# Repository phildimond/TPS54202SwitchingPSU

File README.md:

5V 2A Power Supply using the TI TPS54202

Copyright (c) 2025 Phillip Dimond

Uses my personal favourite switching controller, good for up to 2A.. Changing the FB resistors will change the ouput voltage though efficiency may suffer. Input coltage is designed to be 9V to 25V DC

Released under the Attribution-NonCommercial-ShareAlike 4.0 International license. See the LICENSE file for details. If for some weird reason you want to make a commercial version, please contact me, don't just copy it. My licence fee will be a donation to a charity I'll specify and it's won't be much for a simple project like this.

The Gerbers are laid out in the correct format for JLCPCB, you can simply upload the ZIP file to them and order the boards.

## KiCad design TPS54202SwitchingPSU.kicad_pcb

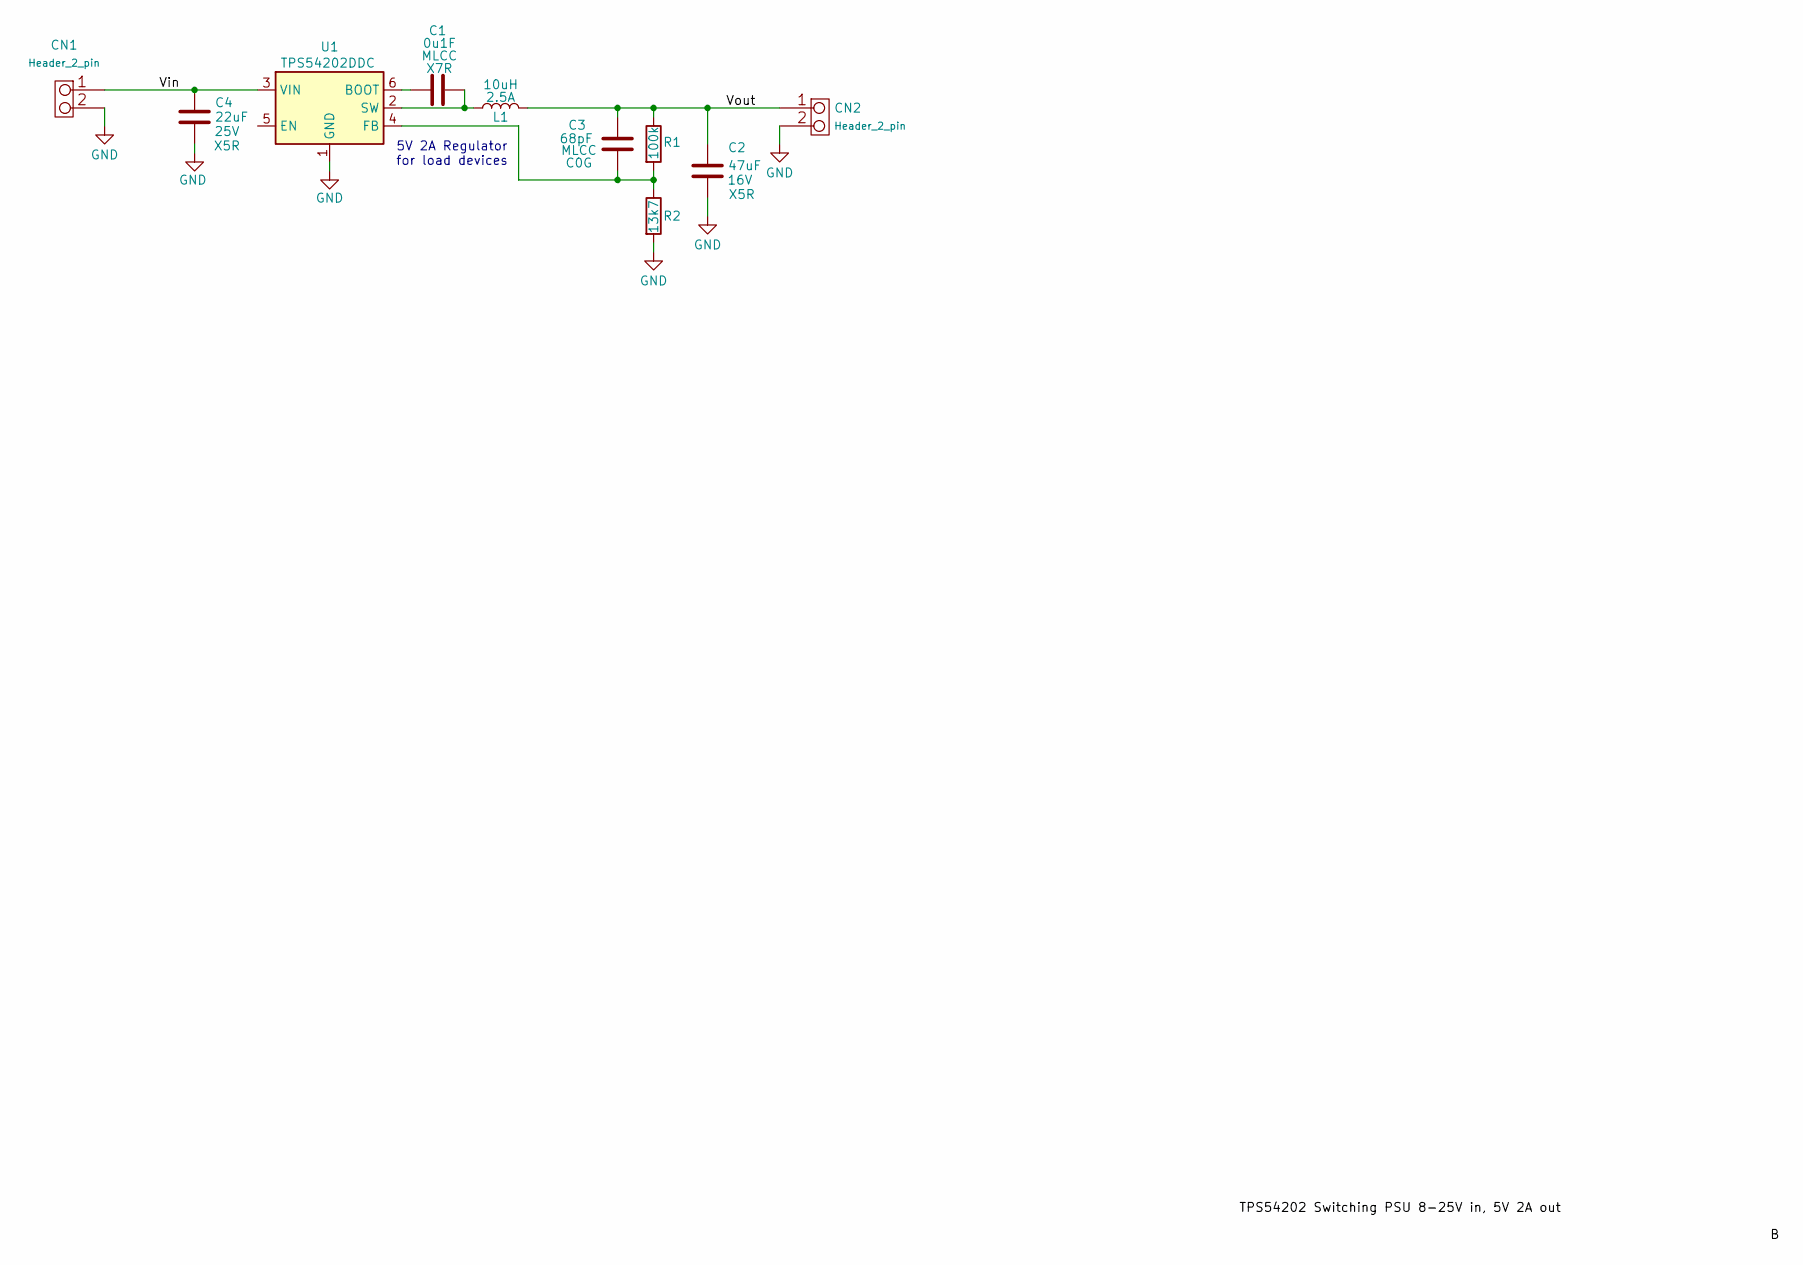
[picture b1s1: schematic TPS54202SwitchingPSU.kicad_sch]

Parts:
C1: 0u1F; C_0805_2012Metric_Pad1.18x1.45mm_HandSolder; LCSC C2167099
C2: 47uF; C_1210_3225Metric_Pad1.33x2.70mm_HandSolder; LCSC C77101
C3: 68pF; C_0805_2012Metric_Pad1.18x1.45mm_HandSolder; LCSC C565680
C4: 22uF; C_1206_3216Metric_Pad1.33x1.80mm_HandSolder; LCSC C12891
CN1, CN2: Header_2_pin; PinHeader_1x02_P2.54mm_Vertical
L1: 10uH; Inductor_TDK_VLS6045EX-150M; LCSC C404502
R1: 100k; R_0805_2012Metric_Pad1.20x1.40mm_HandSolder; LCSC C137393
R2: 13k7; R_0805_2012Metric_Pad1.20x1.40mm_HandSolder; Part YAGEO RC1206FR-0713K7L; LCSC C488637
U1: TPS54202DDC; SOT-23-6

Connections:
/Vin: C4.1, CN1.1, U1.3 (VIN)
/Vout: C2.1, C3.2, CN2.1, L1.2, R1.1
GND: C2.2, C4.2, CN1.2 (PM), CN2.2 (PM), R2.2, U1.1 (GND)
unnamed: C1.1, U1.6 (BOOT)
unnamed: C3.1, R1.2, R2.1, U1.4 (FB)
unnamed: C1.2, L1.1, U1.2 (SW)

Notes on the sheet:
5V 2A Regulator for load devices

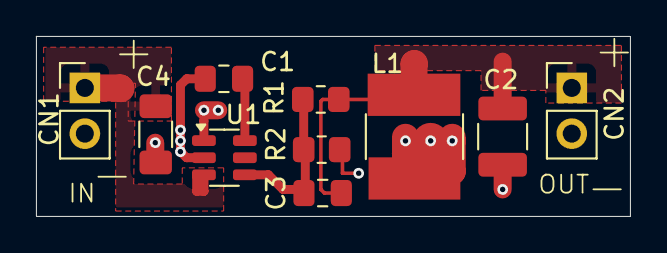
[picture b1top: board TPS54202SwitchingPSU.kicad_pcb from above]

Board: 2 copper layers, 33.0 x 10.0 mm, 10 parts (0 on the bottom side), 6 nets.

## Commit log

2025-07-09 Rev A production release
2025-07-09 Working on electronics - switching PSU
2025-07-19 Updated to Rev B to fix board errors
